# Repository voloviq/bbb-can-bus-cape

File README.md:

# bbb-can-bus-cape
Simple Beaglebone Black CAN bus cape

Board 3D view

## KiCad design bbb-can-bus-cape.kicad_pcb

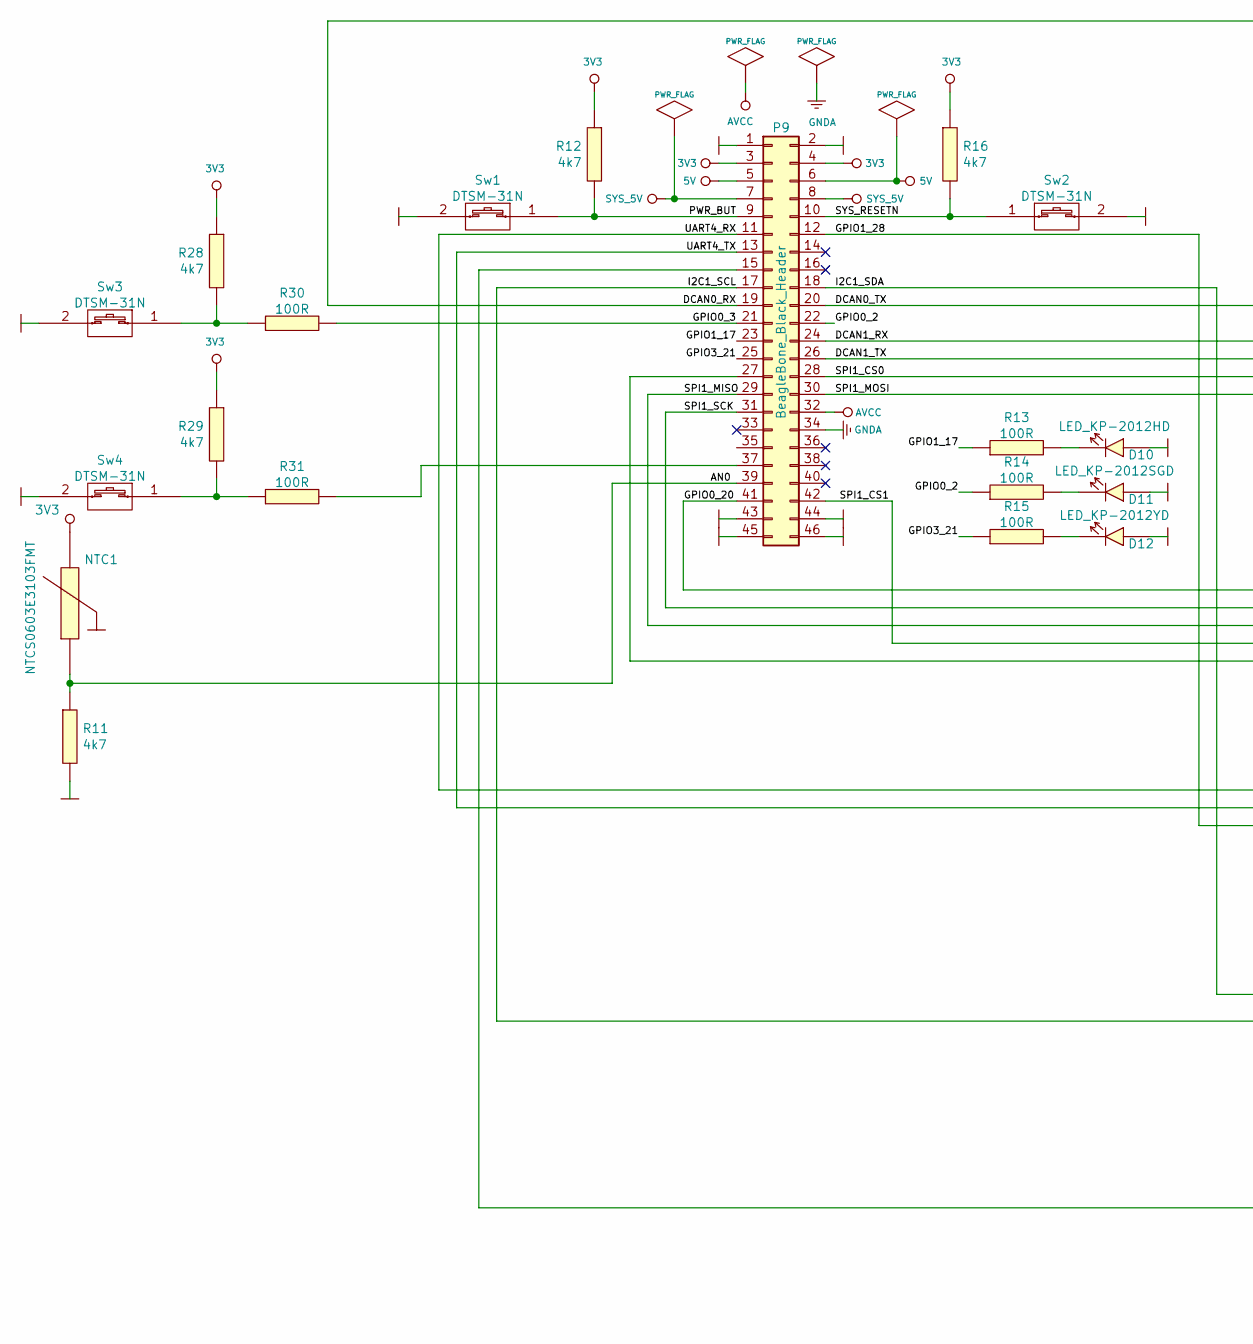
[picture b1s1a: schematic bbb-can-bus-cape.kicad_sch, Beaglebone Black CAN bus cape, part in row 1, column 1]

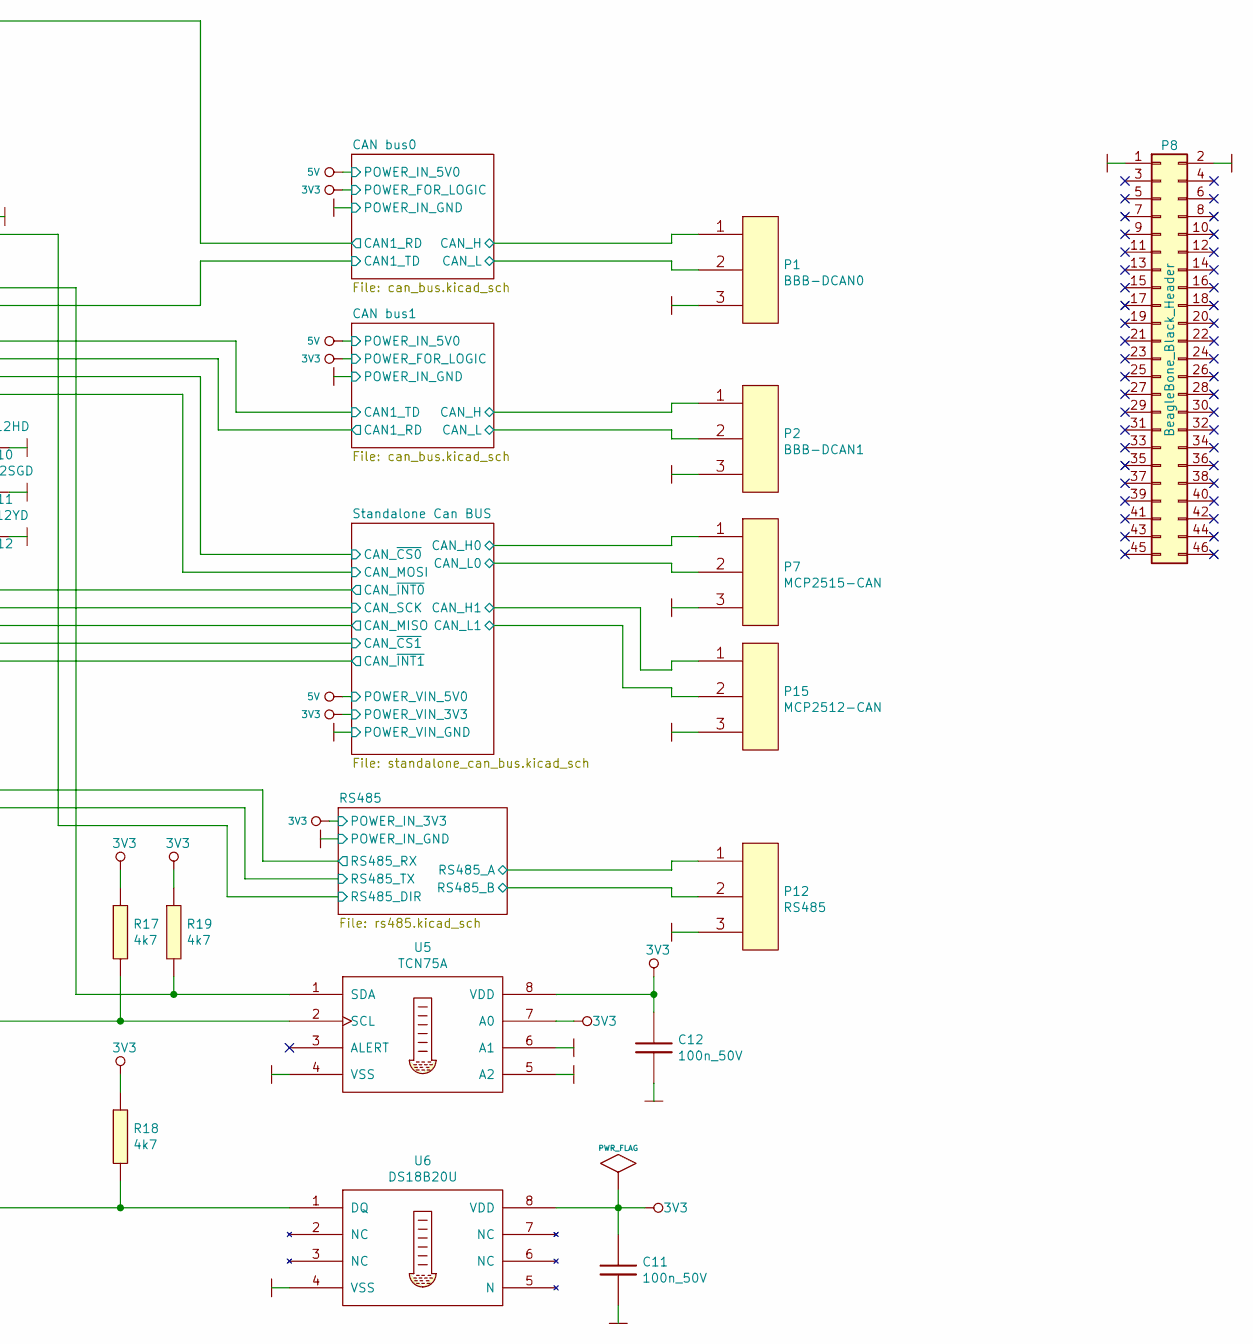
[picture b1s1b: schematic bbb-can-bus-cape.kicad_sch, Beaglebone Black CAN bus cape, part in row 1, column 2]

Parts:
C11, C12: 100n_50V; 100nF_0603; Manufacturer Part Number CL10B104JB8NNNC
D10: LED_KP-2012HD; LED_KP-2012HD_SM0805
D11: LED_KP-2012SGD; LED_KP-2012SGD_SM0805
D12: LED_KP-2012YD; LED_KP-2012YD_SM0805
NTC1: NTCS0603E3103FMT; Manufacturer Part Number NTCG163JF103FT1; LCSC Part # (optional) C76589
P1: BBB-DCAN0; DG301-5.0-03P-12-00A(H); Manufacturer Part Number DG301-5.0-03P-12-00A(H)
P2: BBB-DCAN1; DG301-5.0-03P-12-00A(H); Manufacturer Part Number DG301-5.0-03P-12-00A(H)
P7: MCP2515-CAN; DG301-5.0-03P-12-00A(H); Manufacturer Part Number DG301-5.0-03P-12-00A(H)
P8, P9: BeagleBone_Black_Header; Socket_BeagleBone_Black
P12: RS485; DG301-5.0-03P-12-00A(H); Manufacturer Part Number DG301-5.0-03P-12-00A(H)
P15: MCP2512-CAN; DG301-5.0-03P-12-00A(H); Manufacturer Part Number DG301-5.0-03P-12-00A(H)
R11, R12, R16, R17, R18, R19, R28, R29: 4k7; 4k7_0603; Manufacturer Part Number 0603SAF4701T5E
R13, R14, R15, R30, R31: 100R; 100R_0603; Manufacturer Part Number CQ03SAF1000T5E; LCSC Part #(optional) C269700
Sw1, Sw2, Sw3, Sw4: DTSM-31N; DTSM-31N_SMD
U5: TCN75A; TCN75A_SOIC8
U6: DS18B20U; DS18B20U_MSOP-8_3x3mm_P0.65mm

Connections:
3V3: C11.1, C12.1, NTC1.2, P9.3, P9.4, R12.1, R16.1, R17.1, R18.1, R19.1, R28.1, R29.1, U5.7 (A0), U5.8 (VDD), U6.8 (VDD); also elsewhere on the board
5V: P9.5, P9.6; also elsewhere on the board
/AN0: NTC1.1, P9.39, R11.1
/CAN bus0/CAN_H: P1.1; also elsewhere on the board
/CAN bus0/CAN_L: P1.2; also elsewhere on the board
/CAN bus1/CAN_H: P2.1; also elsewhere on the board
/CAN bus1/CAN_L: P2.2; also elsewhere on the board
/DCAN0_RX: P9.19; also elsewhere on the board
/DCAN0_TX: P9.20; also elsewhere on the board
/DCAN1_RX: P9.24; also elsewhere on the board
/DCAN1_TX: P9.26; also elsewhere on the board
/GPIO0_2: P9.22, R14.1
/GPIO0_3: P9.21, R30.2
/GPIO0_20: P9.41; also elsewhere on the board
/GPIO1_17: P9.23, R13.1
/GPIO1_28: P9.12; also elsewhere on the board
/GPIO3_21: P9.25, R15.1
/I2C1_SCL: P9.17, R17.2, U5.2 (SCL)
/I2C1_SDA: P9.18, R19.2, U5.1 (SDA)
/PWR_BUT: P9.9, R12.2, Sw1.1
/RS485/RS485_A: P12.1; also elsewhere on the board
/RS485/RS485_B: P12.2; also elsewhere on the board
/SPI1_CS0: P9.28; also elsewhere on the board
/SPI1_CS1: P9.42; also elsewhere on the board
/SPI1_MISO: P9.29; also elsewhere on the board
/SPI1_MOSI: P9.30; also elsewhere on the board
/SPI1_SCK: P9.31; also elsewhere on the board
/SYS_RESETN: P9.10, R16.2, Sw2.1
/Standalone Can BUS/CAN_H0: P7.1; also elsewhere on the board
/Standalone Can BUS/CAN_H1: P15.1; also elsewhere on the board
/Standalone Can BUS/CAN_L0: P7.2; also elsewhere on the board
/Standalone Can BUS/CAN_L1: P15.2; also elsewhere on the board
/Standalone Can BUS/CAN_~INT1~: P9.27; also elsewhere on the board
/UART4_RX: P9.11; also elsewhere on the board
/UART4_TX: P9.13; also elsewhere on the board
GND: C11.2, C12.2, D10.1 (A), D11.1 (A), D12.1 (A), P1.3, P2.3, P7.3, P8.1, P8.2, P9.1, P9.2, P9.43, P9.44, P9.45, P9.46, P12.3, P15.3, R11.2, Sw1.2, Sw2.2, Sw3.2, Sw4.2, U5.4 (VSS), U5.5 (A2), U5.6 (A1), U6.4 (VSS); also elsewhere on the board
unnamed: D10.2 (K), R13.2
unnamed: D11.2 (K), R14.2
unnamed: D12.2 (K), R15.2
unnamed: P9.15, R18.2, U6.1 (DQ)
unnamed: P9.37, R31.2
unnamed: R28.2, R30.1, Sw3.1
unnamed: R29.2, R31.1, Sw4.1
SYS_5V: P9.7, P9.8

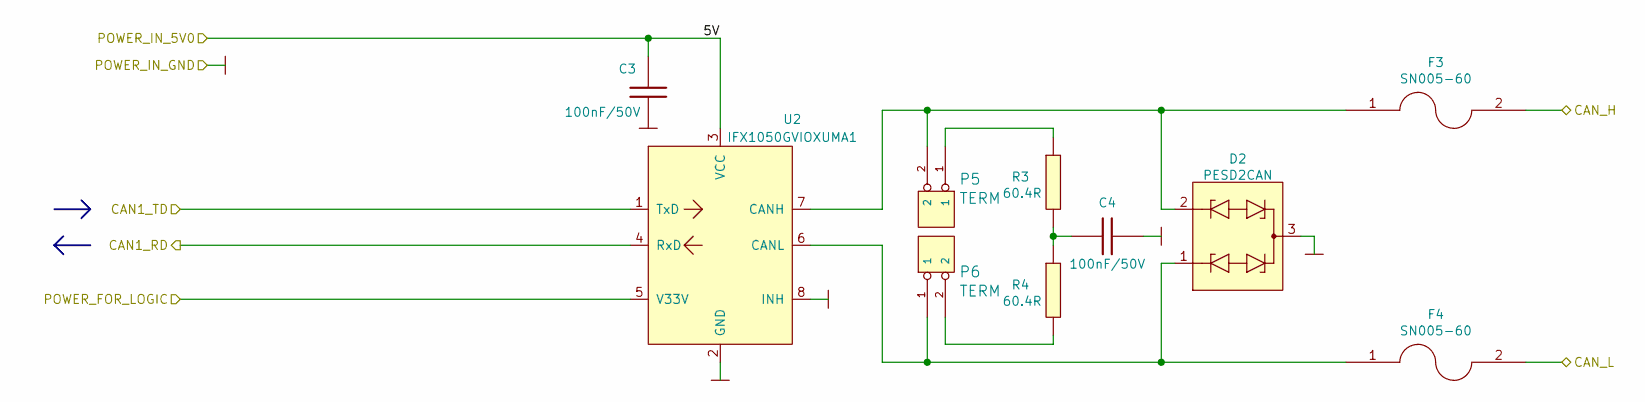
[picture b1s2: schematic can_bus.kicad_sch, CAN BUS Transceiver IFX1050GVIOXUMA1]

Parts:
C3, C4: 100nF/50V; 100nF_0603; Manufacturer Part Number CL10B104JB8NNNC
D2: PESD2CAN; PESD2CAN.215; Manufacturer Part Number PESD2CAN.215; LCSC Part #(optional) C75176
F3, F4: SN005-60; Manufacturer Part Number SN005-60
P5, P6: TERM; Goldpin_2_2_54mm
R3, R4: 60.4R; 60.4R_0805; Maunufacturer Part Numb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 CQ05S8F604JT5E; LCSC Part #(optional) C441730
U2: IFX1050GVIOXUMA1

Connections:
3V3: U2.5 (V33V); also elsewhere on the board
5V: C3.1, U2.3 (VCC); also elsewhere on the board
/CAN bus1/CAN_H: F3.2; also elsewhere on the board
/CAN bus1/CAN_L: F4.2; also elsewhere on the board
/DCAN1_RX: U2.1 (TxD); also elsewhere on the board
/DCAN1_TX: U2.4 (RxD); also elsewhere on the board
GND: C3.2, C4.2, D2.3 (GND), U2.2 (GND), U2.8 (INH); also elsewhere on the board
unnamed: C4.1, R3.2, R4.1
unnamed: D2.1 (I/O1), F4.1, P6.1, U2.6 (CANL)
unnamed: D2.2 (I/O2), F3.1, P5.2, U2.7 (CANH)
unnamed: P5.1, R3.1
unnamed: P6.2, R4.2

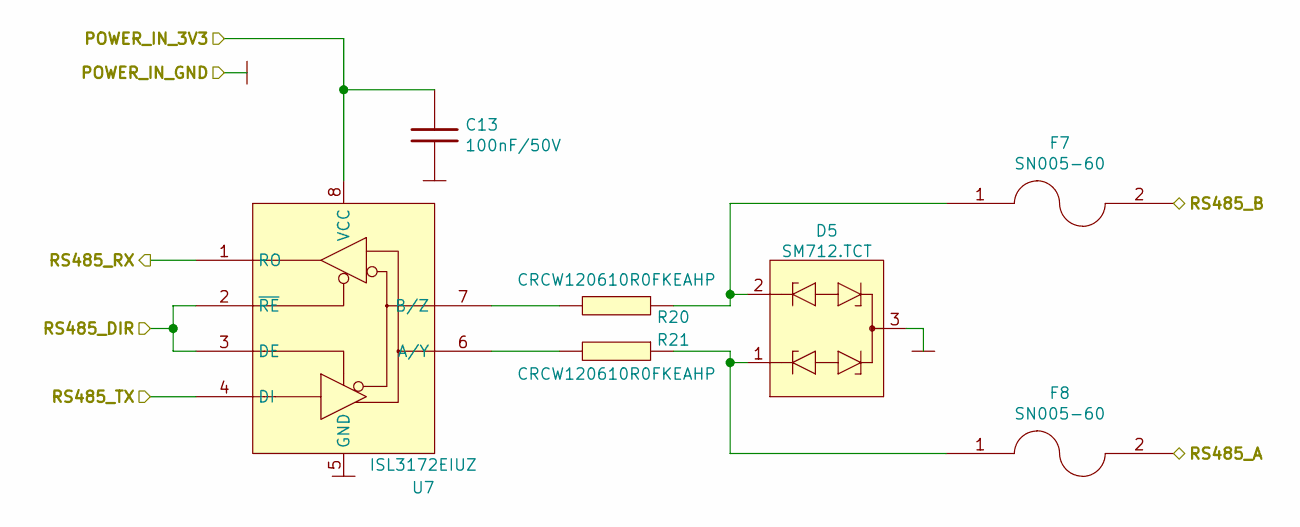
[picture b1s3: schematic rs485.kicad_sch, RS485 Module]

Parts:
C13: 100nF/50V; 100nF_0603; Manufacturer Part Number CL10B104JB8NNNC
D5: SM712.TCT; Manufacturer Part Number SM712.TCT; LCSC Part #(optional) C12067
F7, F8: SN005-60; Manufacturer Part Number SN005-60
R20, R21: CRCW120610R0FKEAHP; Manufacturer Part Number CRCW120610R0FKEAHP
U7: ISL3172EIUZ; Manufacturer Part Number ISL3172EIUZ

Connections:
3V3: C13.1, U7.8 (VCC); also elsewhere on the board
/GPIO1_28: U7.2 (~RE), U7.3 (DE); also elsewhere on the board
/RS485/RS485_A: F8.2; also elsewhere on the board
/RS485/RS485_B: F7.2; also elsewhere on the board
/UART4_RX: U7.1 (RO); also elsewhere on the board
/UART4_TX: U7.4 (DI); also elsewhere on the board
GND: C13.2, D5.3 (GND), U7.5 (GND); also elsewhere on the board
unnamed: D5.1 (I/O1), F8.1, R21.1
unnamed: D5.2 (I/O2), F7.1, R20.1
unnamed: R20.2, U7.7 (B/Z)
unnamed: R21.2, U7.6 (A/Y)

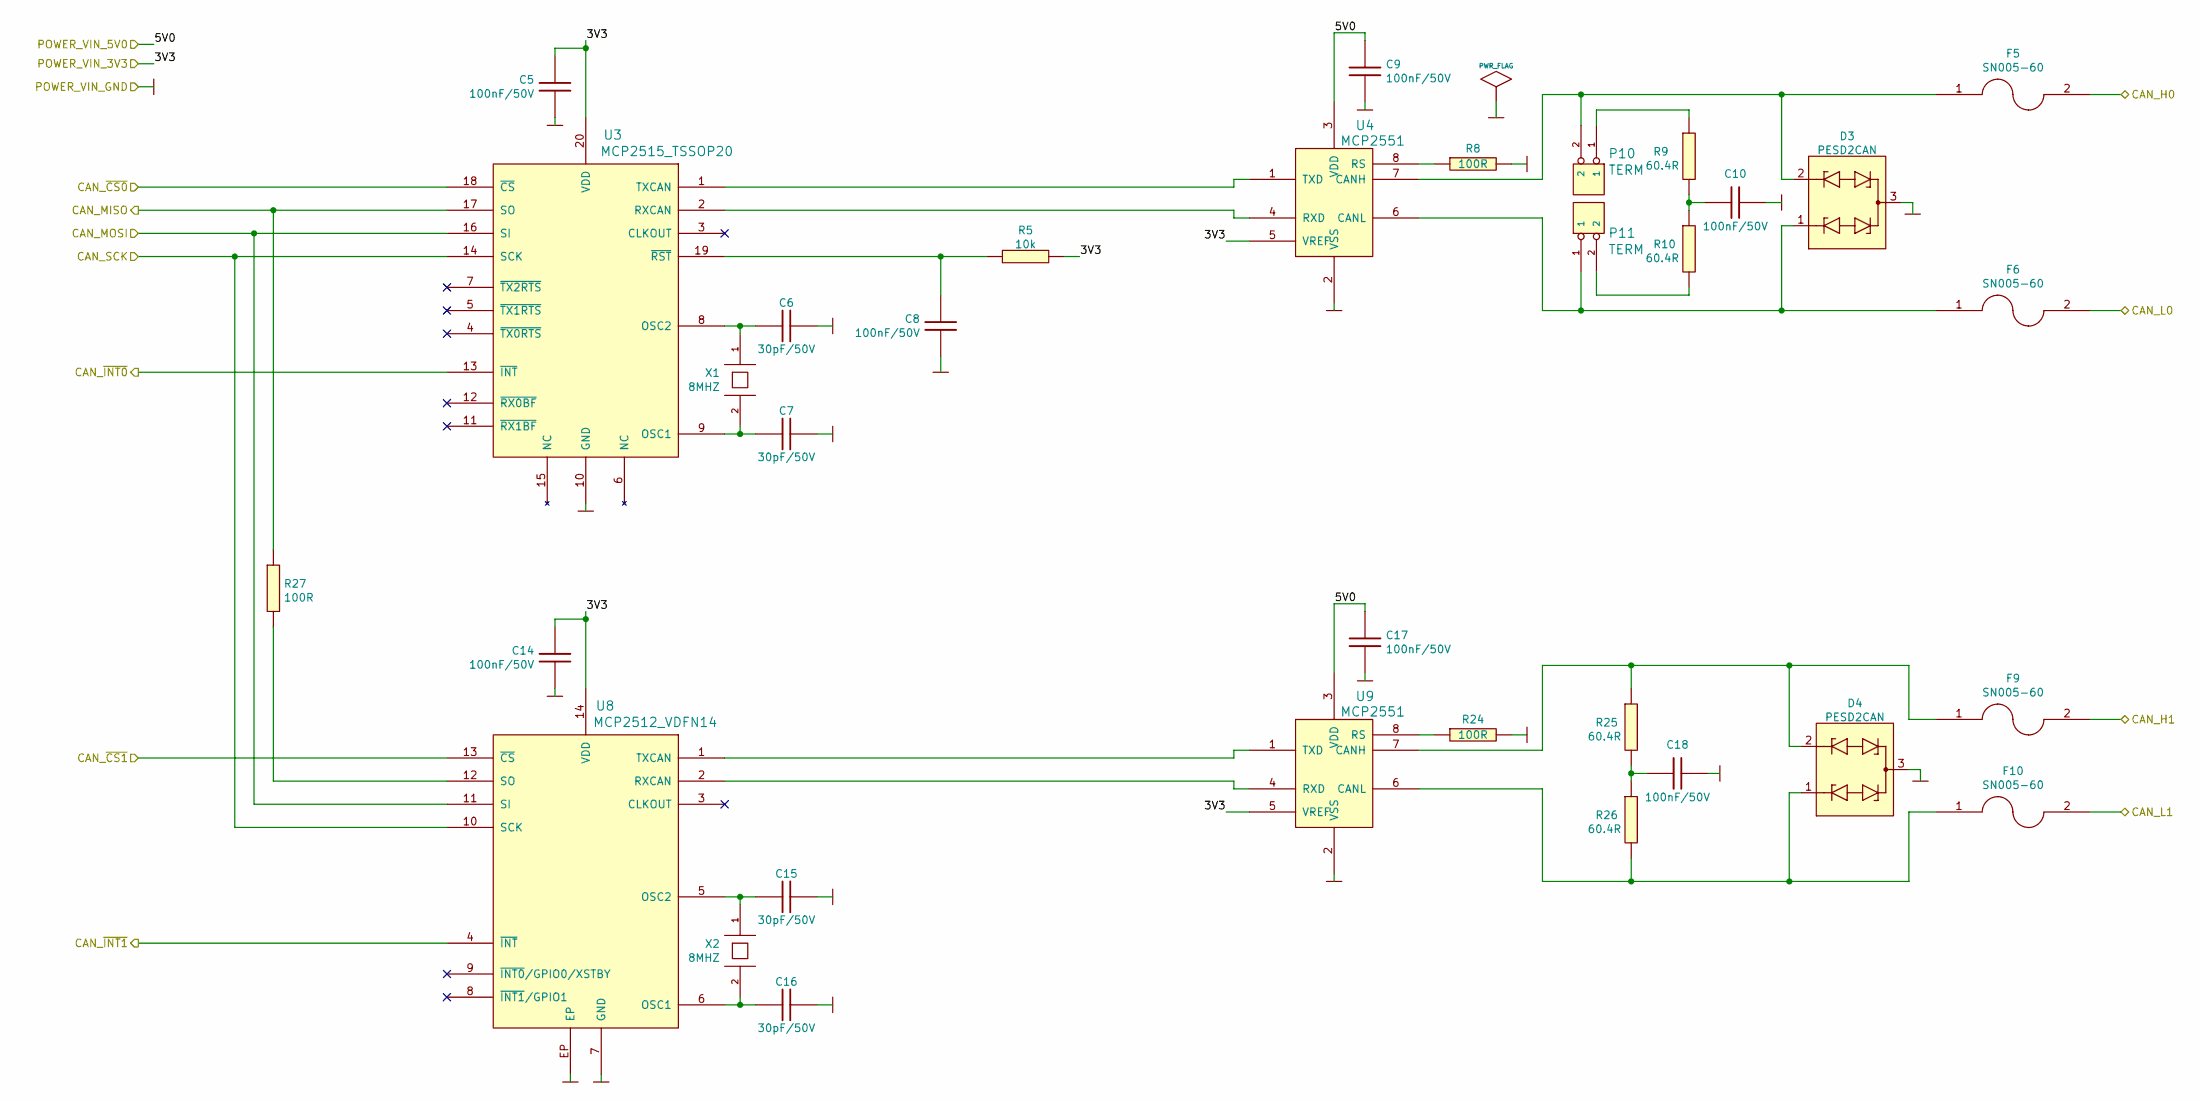
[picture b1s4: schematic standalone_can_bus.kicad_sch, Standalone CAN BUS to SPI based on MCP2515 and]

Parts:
C5, C8, C9, C10, C14, C17, C18: 100nF/50V; 100nF_0603; Manufacturer Part Number CL10B104JB8NNNC
C6, C7, C15, C16: 30pF/50V; 30pF_0603
D3, D4: PESD2CAN; PESD2CAN.215; Manufacturer Part Number PESD2CAN.215; LCSC Part #(optional) C75176
F5, F6, F9, F10: SN005-60; Manufacturer Part Number SN005-60
P10, P11: TERM; Goldpin_2_2_54mm
R5: 10k; 10k_0603; Manufacturer Part Number 0603SAJ0103T5E
R8, R24, R27: 100R; 100R_0603; Manufacturer Part Number CQ03SAF1000T5E; LCSC Part #(optional) C269700
R9, R10, R25, R26: 60.4R; 60.4R_0805; Maunufacturer Part Numb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 CQ05S8F604JT5E; LCSC Part #(optional) C441730
U3: MCP2515_TSSOP20; MCP2515-I-TSSOP20; Manufacturer Part Number MCP2515-I/ST; LCSC Part # (optional) C15193
U4, U9: MCP2551; MCP2551_SO8
U8: MCP2512_VDFN14; Manufacturer Part Number MCP2515-I/ML; LCSC Part # (optional) C191563
X1, X2: 8MHZ; ABM3AIG-8.000MHZ-8-1R-T; Manufacturer Part Number ABM3AIG-8.000MHZ-8-1R-T

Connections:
3V3: C5.1, C14.1, R5.2, U3.20 (VDD), U4.5 (VREF), U8.14 (VDD), U9.5 (VREF); also elsewhere on the board
5V: C9.1, C17.1, U4.3 (VDD), U9.3 (VDD); also elsewhere on the board
/GPIO0_20: U3.13 (~INT); also elsewhere on the board
/SPI1_CS0: U3.18 (~CS); also elsewhere on the board
/SPI1_CS1: U8.13 (~CS); also elsewhere on the board
/SPI1_MISO: R27.1, U3.17 (SO); also elsewhere on the board
/SPI1_MOSI: U3.16 (SI), U8.11 (SI); also elsewhere on the board
/SPI1_SCK: U3.14 (SCK), U8.10 (SCK); also elsewhere on the board
/Standalone Can BUS/CAN_H0: F5.2; also elsewhere on the board
/Standalone Can BUS/CAN_H1: F9.2; also elsewhere on the board
/Standalone Can BUS/CAN_L0: F6.2; also elsewhere on the board
/Standalone Can BUS/CAN_L1: F10.2; also elsewhere on the board
/Standalone Can BUS/CAN_~INT1~: U8.4 (~INT); also elsewhere on the board
GND: C5.2, C6.2, C7.2, C8.2, C9.2, C10.2, C14.2, C15.2, C16.2, C17.2, C18.2, D3.3 (GND), D4.3 (GND), R8.2, R24.2, U3.10 (GND), U4.2 (VSS), U8.7 (GND), U8.EP, U9.2 (VSS); also elsewhere on the board
unnamed: C6.1, U3.8 (OSC2), X1.1
unnamed: C7.1, U3.9 (OSC1), X1.2
unnamed: C8.1, R5.1, U3.19 (~RST)
unnamed: C10.1, R9.2, R10.1
unnamed: C15.1, U8.5 (OSC2), X2.1
unnamed: C16.1, U8.6 (OSC1), X2.2
unnamed: C18.1, R25.2, R26.1
unnamed: D3.1 (I/O1), F6.1, P11.1, U4.6 (CANL)
unnamed: D3.2 (I/O2), F5.1, P10.2, U4.7 (CANH)
unnamed: D4.1 (I/O1), F10.1, R26.2, U9.6 (CANL)
unnamed: D4.2 (I/O2), F9.1, R25.1, U9.7 (CANH)
unnamed: P10.1, R9.1
unnamed: P11.2, R10.2
unnamed: R8.1, U4.8 (RS)
unnamed: R24.1, U9.8 (RS)
unnamed: R27.2, U8.12 (SO)
unnamed: U3.1 (TXCAN), U4.1 (TXD)
unnamed: U3.2 (RXCAN), U4.4 (RXD)
unnamed: U8.1 (TXCAN), U9.1 (TXD)
unnamed: U8.2 (RXCAN), U9.4 (RXD)

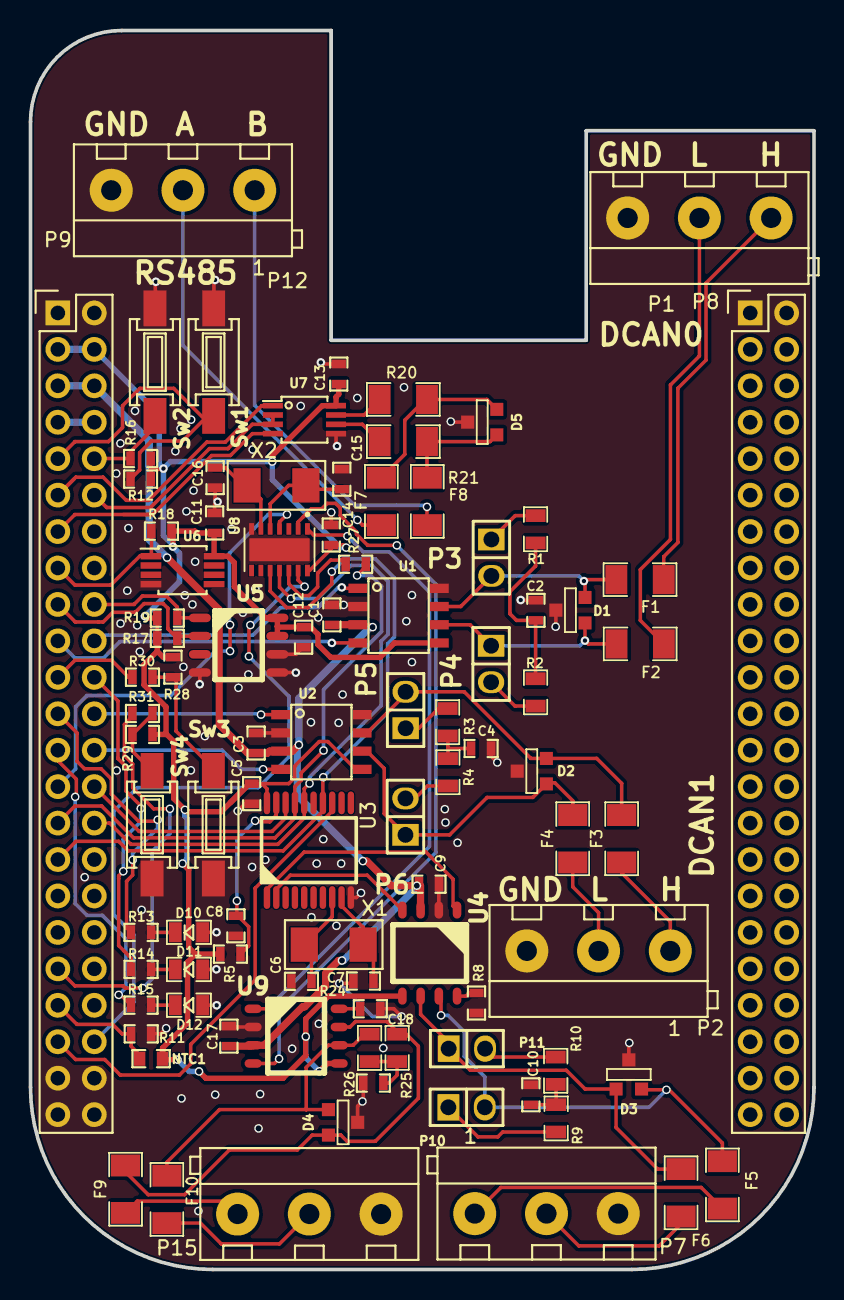
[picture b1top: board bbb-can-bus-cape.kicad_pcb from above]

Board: 2 copper layers, 54.6 x 86.4 mm, 92 parts (0 on the bottom side), 78 nets.

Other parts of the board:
C1, C2: 100nF/50V; 100nF_0603
D1: PESD2CAN; PESD2CAN.215
F1, F2: SN005-60
P3, P4: TERM; Goldpin_2_2_54mm
R1, R2: 60.4R; 60.4R_0805
U1: IFX1050GVIOXUMA1

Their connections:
3V3: U1.5 (V33V); also elsewhere on the board
5V: C1.1, U1.3 (VCC); also elsewhere on the board
/CAN bus0/CAN_H: F1.2; also elsewhere on the board
/CAN bus0/CAN_L: F2.2; also elsewhere on the board
/DCAN0_RX: U1.4 (RxD); also elsewhere on the board
/DCAN0_TX: U1.1 (TxD); also elsewhere on the board
GND: C1.2, C2.2, D1.3 (GND), U1.2 (GND), U1.8 (INH); also elsewhere on the board
unnamed: C2.1, R1.2, R2.1
unnamed: D1.1 (I/O1), F2.1, P4.1, U1.6 (CANL)
unnamed: D1.2 (I/O2), F1.1, P3.2, U1.7 (CANH)
unnamed: P3.1, R1.1
unnamed: P4.2, R2.2

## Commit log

2021-04-09 Initial
2021-04-10 Added elements and hierarchical sheets
2021-04-10 Schematic checked
2021-04-12 Finalized project
2021-04-29 Regenerated gerbers
